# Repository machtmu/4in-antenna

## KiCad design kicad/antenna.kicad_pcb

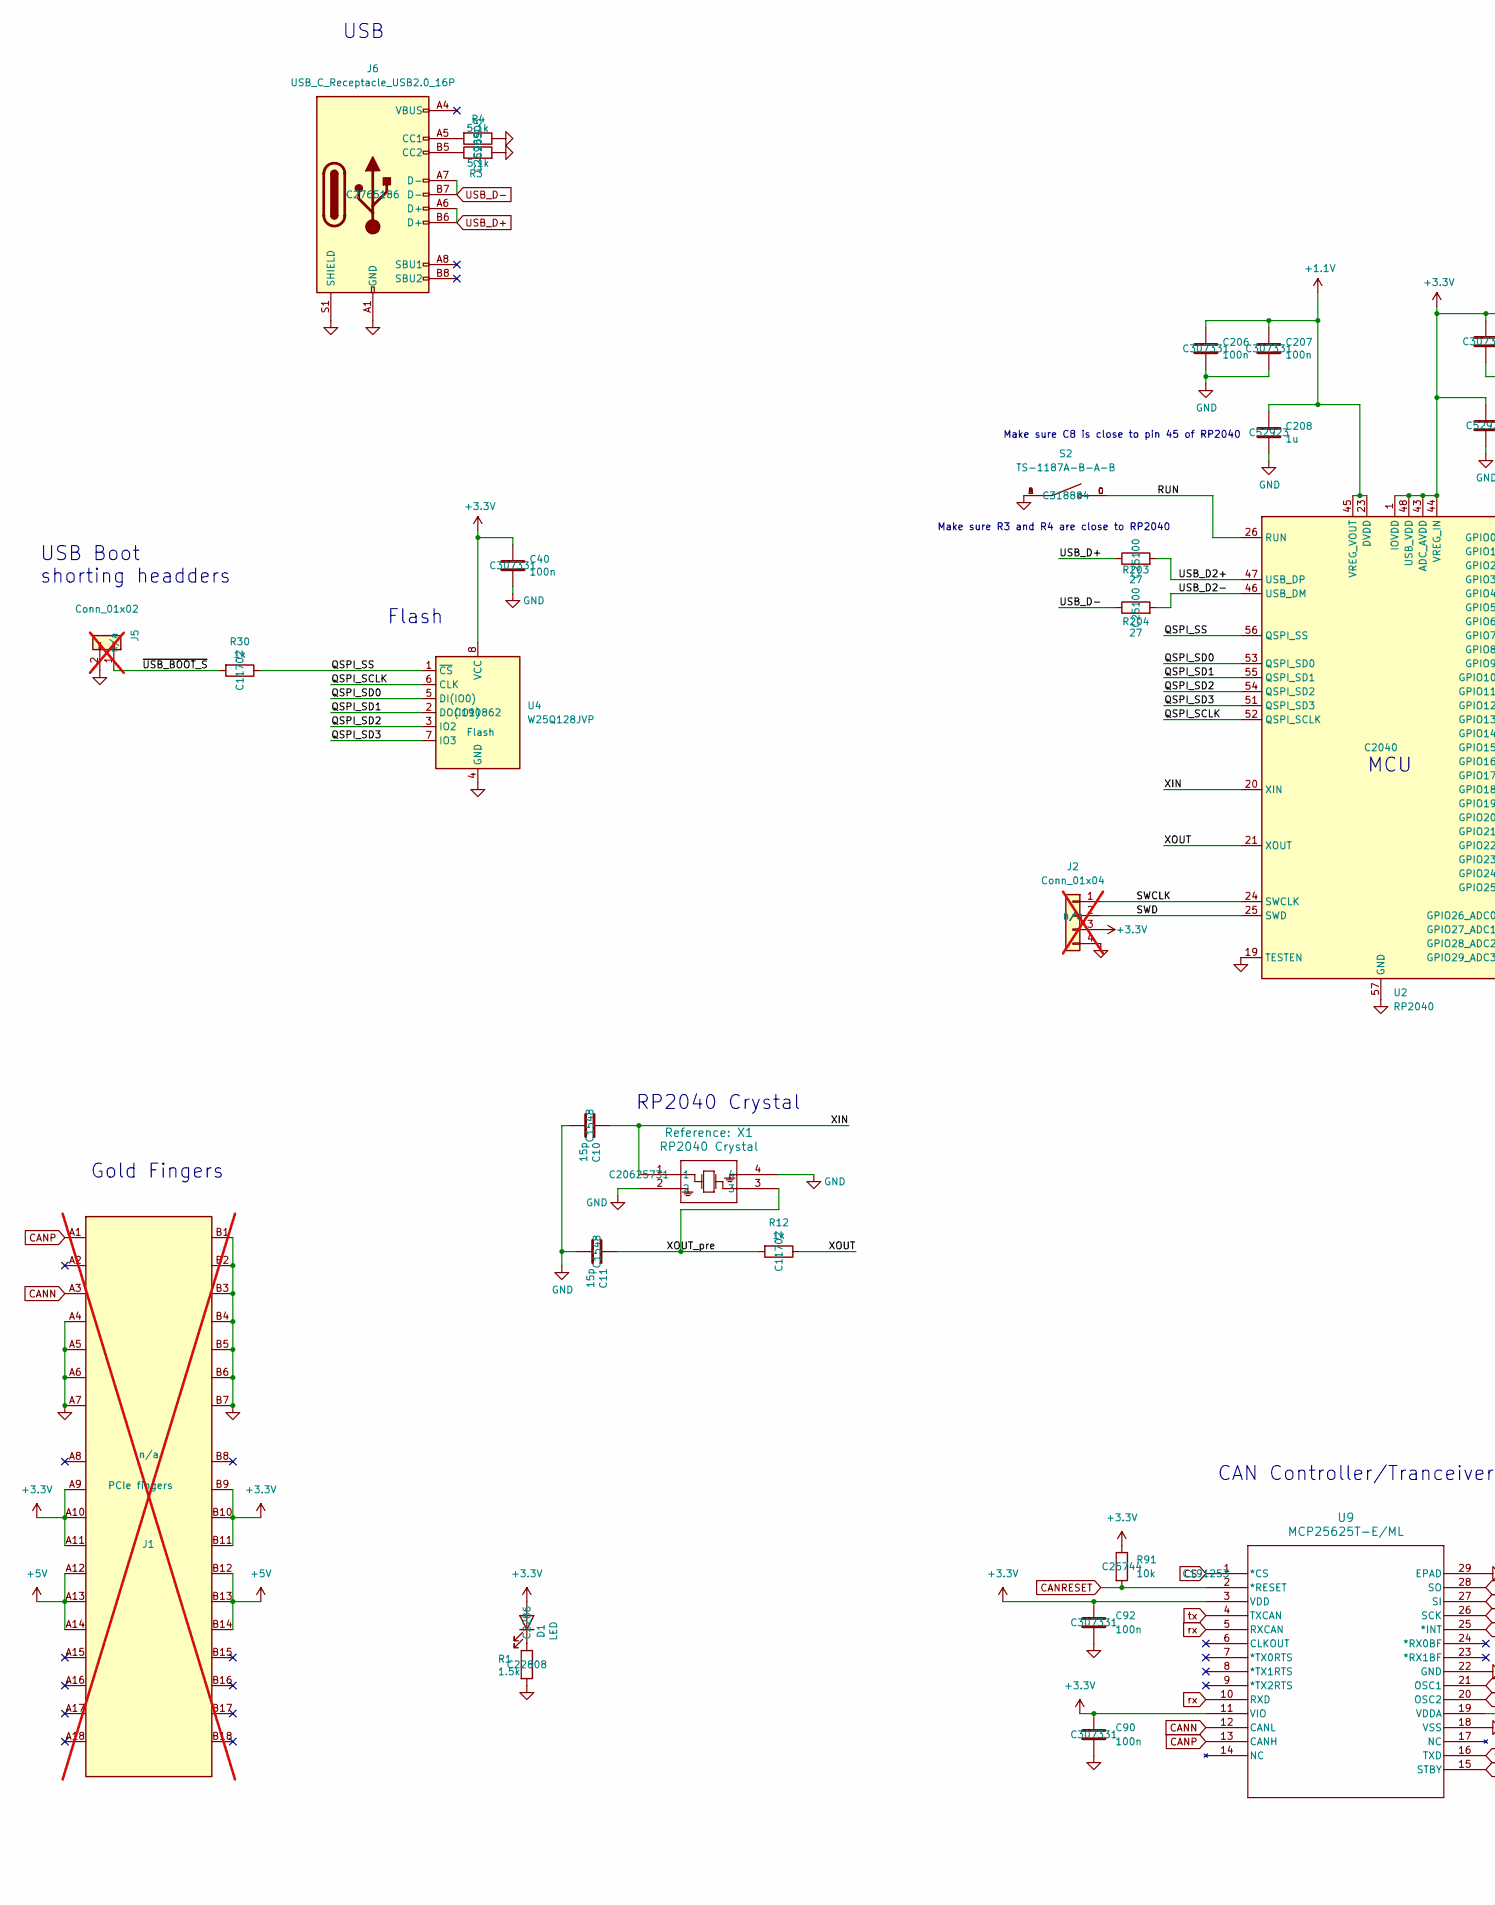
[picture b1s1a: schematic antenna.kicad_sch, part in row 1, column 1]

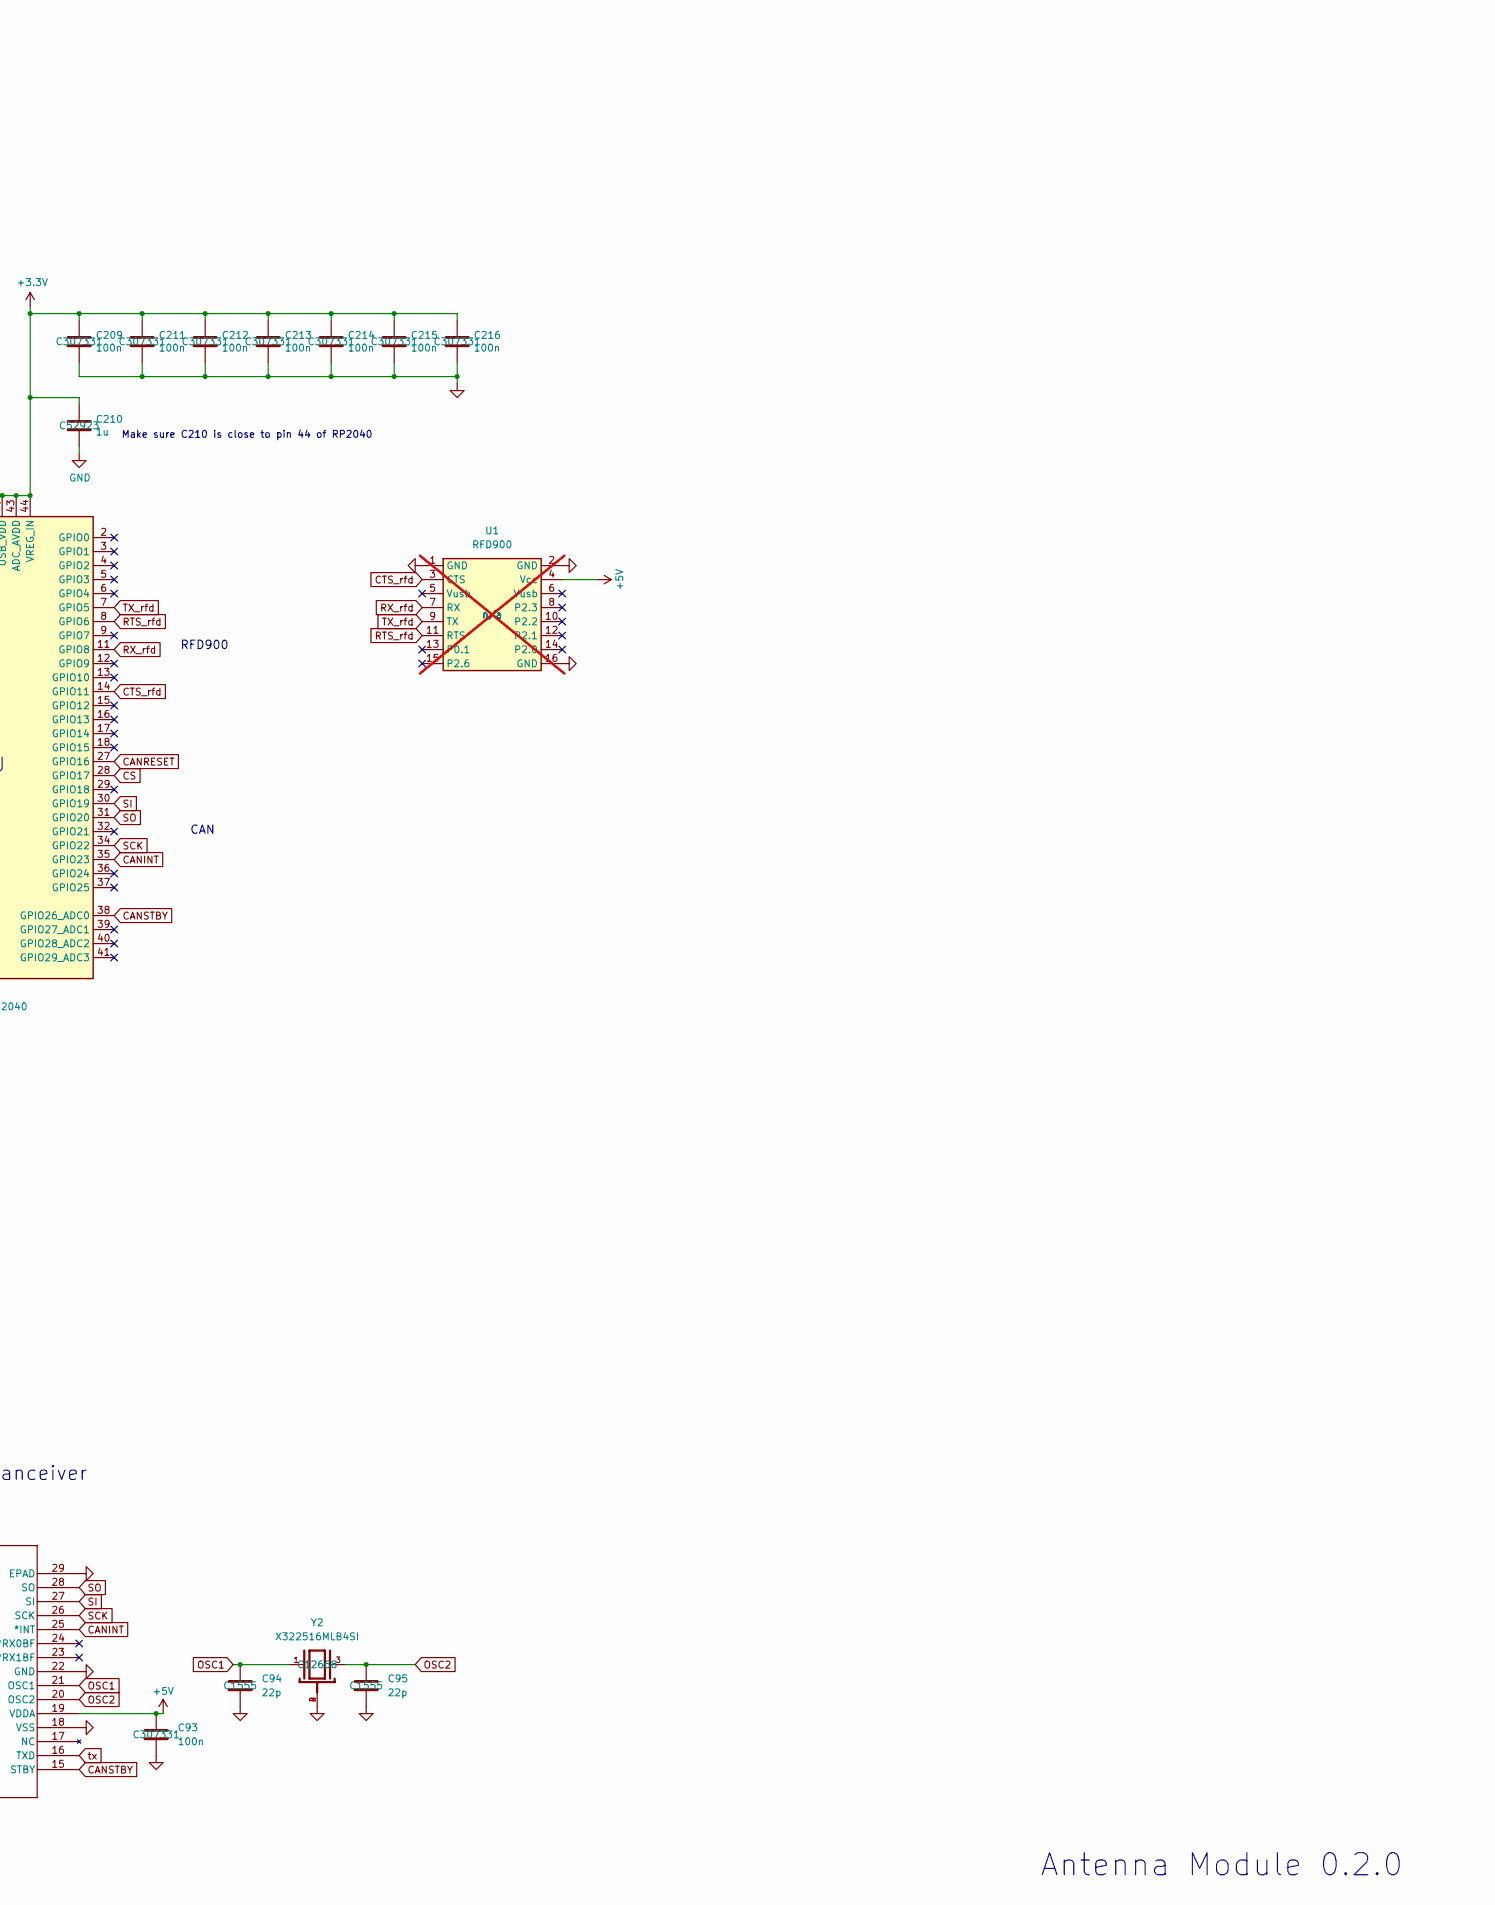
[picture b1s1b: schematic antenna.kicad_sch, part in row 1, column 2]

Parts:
C10, C11: 15p; C_0402_1005Metric; LCSC Part # C1548
C40, C90, C92, C93, C206, C207, C209, C211, C212, C213, C214, C215, C216: 100n; C_0402_1005Metric; LCSC Part # C307331
C94, C95: 22p; C_0402_1005Metric; LCSC Part # C1555
C208, C210: 1u; C_0402_1005Metric; LCSC Part # C52923
D1: LED; LED_0603_1608Metric; LCSC Part # C2286
J1: Bus_PCI_Express_x1; BUS_PCIexpress_x1; LCSC Part # n/a; not fitted
J2: Conn_01x04; NS-Tech_Grove_1x04_P2mm_Vertical; LCSC PN n/a; not fitted
J5: Conn_01x02; PinHeader_1x02_P2.54mm_Vertical; LCSC Part # n/a; not fitted
J6: USB_C_Receptacle_USB2.0_16P; USB_C_Receptacle_Palconn_UTC16-G; LCSC Part # C2765186
R1: 1.5k; R_0603_1608Metric; LCSC Part # C22808
R3, R4: 5.1k; R_0402_1005Metric; LCSC Part # C25905
R12, R30: 1k; R_0402_1005Metric; LCSC Part # C11702
R91: 10k; R_0402_1005Metric; LCSC Part # C25744
R203, R204: 27; R_0402_1005Metric; LCSC Part # C25100
S2: TS-1187A-B-A-B; Manufacturer PN TS-1187A-B-A-B; LCSC PN C318884
U1: RFD900; LCSC PN n/a; not fitted
U2: RP2040; QFN-56-1EP_7x7mm_P0.4mm_EP3.2x3.2mm; LCSC C2040
U4: W25Q128JVP; WSON-8-1EP_6x5mm_P1.27mm_EP3.4x4.3mm; LCSC C190862
U9: MCP25625T-E/ML; QFN28_6X6MC_MCH; LCSC PN C191253
X1: RP2040 Crystal; ABM8-272-T3_ABR; Manufacturer PN ABM8-272-T3_ABR; LCSC PN C20625731
Y2: X322516MLB4SI; LCSC PN C12668

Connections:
+1.1V: C206.1, C207.1, C208.1, U2.23 (DVDD), U2.45 (VREG_VOUT), U2.50 (DVDD)
+3.3V: C40.1, C90.1, C92.1, C209.1, C210.1, C211.1, C212.1, C213.1, C214.1, C215.1, C216.1, D1.2 (A), J1.A9 (+3.3V), J1.A10 (+3.3V), J1.A11 (~PERST), J1.B9 (JTAG1), J1.B10 (3.3Vaux), J1.B11 (~WAKE), J2.3, R91.1, U2.1 (IOVDD), U2.10 (IOVDD), U2.22 (IOVDD), U2.33 (IOVDD), U2.42 (IOVDD), U2.43 (ADC_AVDD), U2.44 (VREG_IN), U2.48 (USB_VDD), U2.49 (IOVDD), U4.8 (VCC), U9.3 (VDD), U9.11 (VIO)
+5V: C93.1, J1.A12 (GND), J1.A13 (REFCLK+), J1.A14 (REFCLK-), J1.B12 (RSVD), J1.B13 (GND), J1.B14 (PETp0), U1.4 (Vcc), U9.19 (VDDA)
/QSPI_SCLK: U2.52 (QSPI_SCLK), U4.6 (CLK)
/QSPI_SD0: U2.53 (QSPI_SD0), U4.5 (DI(IO0))
/QSPI_SD1: U2.55 (QSPI_SD1), U4.2 (DO(IO1))
/QSPI_SD2: U2.54 (QSPI_SD2), U4.3 (IO2)
/QSPI_SD3: U2.51 (QSPI_SD3), U4.7 (IO3)
/QSPI_SS: R30.1, U2.56 (QSPI_SS), U4.1 (~CS)
/RUN: S2.C, S2.D, U2.26 (RUN)
/SWCLK: J2.1, U2.24 (SWCLK)
/SWD: J2.2, U2.25 (SWD)
/USB_D2+: R203.2, U2.47 (USB_DP)
/USB_D2-: R204.2, U2.46 (USB_DM)
/XIN: C10.1, U2.20 (XIN), X1.1
/XOUT: R12.1, U2.21 (XOUT)
/XOUT_pre: C11.1, R12.2, X1.3
/~USB_BOOT_S: J5.1, R30.2
CANINT: U2.35 (GPIO23), U9.25 (*INT)
CANN: J1.A3 (+12V), U9.12 (CANL)
CANP: J1.A1 (~PRSNT1), U9.13 (CANH)
CANRESET: R91.2, U2.27 (GPIO16), U9.2 (*RESET)
CANSTBY: U2.38 (GPIO26_ADC0), U9.15 (STBY)
CS: U2.28 (GPIO17), U9.1 (*CS)
CTS_rfd: U1.3 (CTS), U2.14 (GPIO11)
GND: C10.2, C11.2, C40.2, C90.2, C92.2, C93.2, C94.2, C95.2, C206.2, C207.2, C208.2, C209.2, C210.2, C211.2, C212.2, C213.2, C214.2, C215.2, C216.2, J1.A4 (GND), J1.A5 (JTAG2), J1.A6 (JTAG3), J1.A7 (JTAG4), J1.B1 (+12V), J1.B2 (+12V), J1.B3 (+12V), J1.B4 (GND), J1.B5 (SMCLK), J1.B6 (SMDAT), J1.B7 (GND), J2.4, J5.2, J6.A1 (GND), J6.A12 (GND), J6.B1 (GND), J6.B12 (GND), J6.S1 (SHIELD), R1.2, R3.2, R4.1, S2.A, S2.B, U1.1 (GND), U1.2 (GND), U1.16 (GND), U2.19 (TESTEN), U2.57 (GND), U4.4 (GND), U9.18 (VSS), U9.22 (GND), U9.29 (EPAD), X1.2, X1.4, Y2.2, Y2.4
unnamed: D1.1 (K), R1.1
unnamed: J6.A5 (CC1), R4.2
unnamed: J6.B5 (CC2), R3.1
OSC1: C94.1, U9.21 (OSC1), Y2.1
OSC2: C95.1, U9.20 (OSC2), Y2.3
RTS_rfd: U1.11 (RTS), U2.8 (GPIO6)
RX_rfd: U1.7 (RX), U2.11 (GPIO8)
SCK: U2.34 (GPIO22), U9.26 (SCK)
SI: U2.30 (GPIO19), U9.27 (SI)
SO: U2.31 (GPIO20), U9.28 (SO)
TX_rfd: U1.9 (TX), U2.7 (GPIO5)
USB_D+: J6.A6 (D+), J6.B6 (D+), R203.1
USB_D-: J6.A7 (D-), J6.B7 (D-), R204.1
rx: U9.5 (RXCAN), U9.10 (RXD)
tx: U9.4 (TXCAN), U9.16 (TXD)

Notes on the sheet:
Make sure C210 is close to pin 44 of RP2040
Make sure C8 is close to pin 45 of RP2040
RP2040 Crystal
USB
Make sure R3 and R4 are close to RP2040
CAN
RFD900
USB Boot shorting headders
Antenna Module 0.2.0
Gold Fingers
MCU
CAN Controller/Tranceiver
Flash

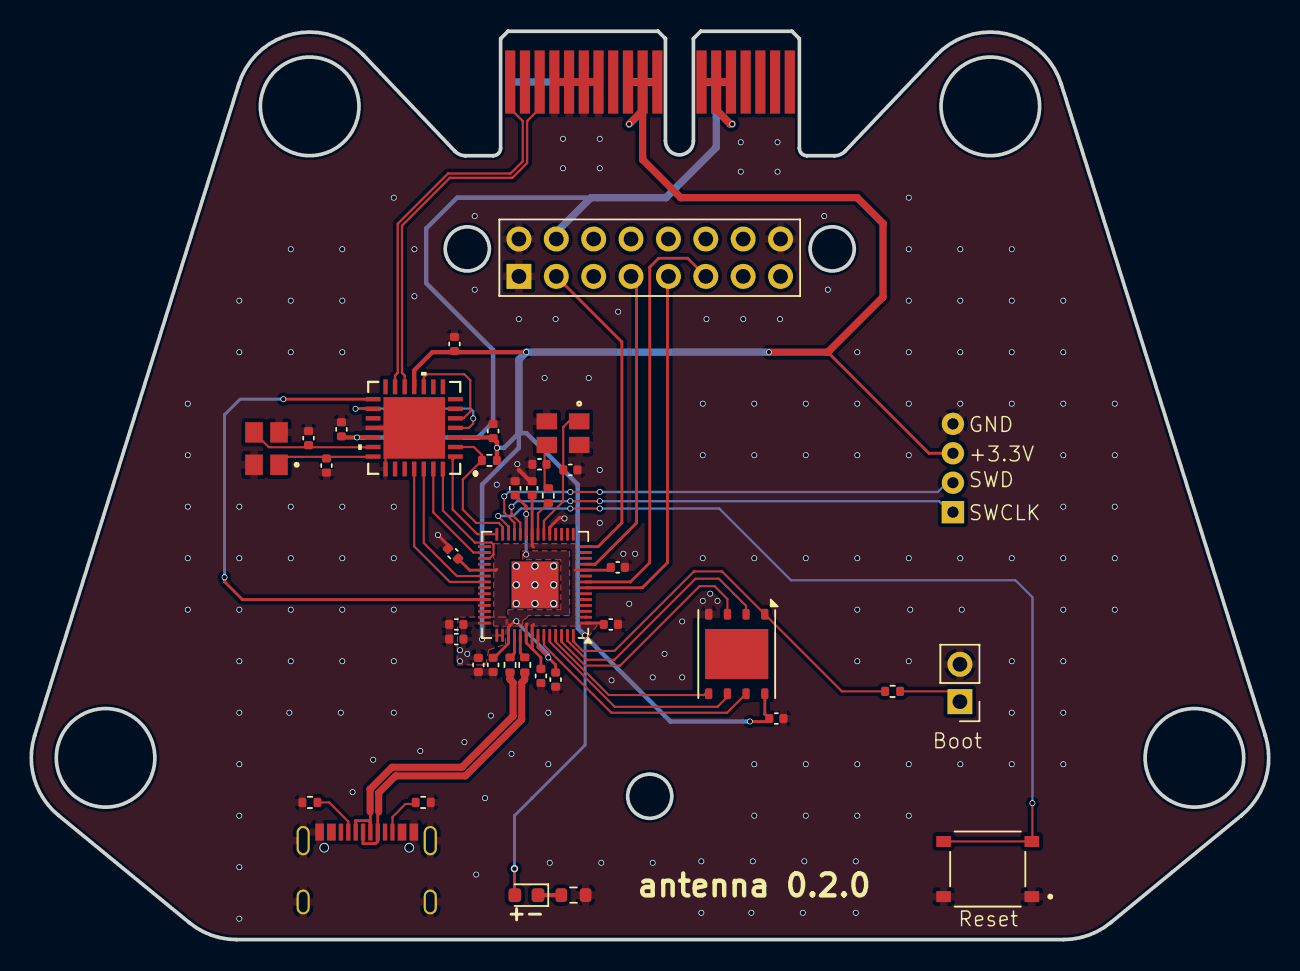
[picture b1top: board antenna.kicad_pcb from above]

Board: 2 copper layers, 84.1 x 61.7 mm, 39 parts (1 on the bottom side), 41 nets.

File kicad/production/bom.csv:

Designator,Footprint,Quantity,Value,LCSC Part #
"C10, C11",0402,2,15p,C1548
"C206, C207, C209, C211, C212, C213, C214, C215, C216, C40, C90, C92, C93",0402,13,100n,C307331
"C208, C210",0402,2,1u,C52923
"C94, C95",0402,2,22p,C1555
D1,0603,1,LED,C2286
J6,USB_C_Receptacle_Palconn_UTC16-G,1,USB_C_Receptacle_USB2.0_16P,C2765186
R1,0603,1,1.5k,C22808
"R12, R30",0402,2,1k,C11702
"R203, R204",0402,2,27,C25100
"R3, R4",0402,2,5.1k,C25905
R91,0402,1,10k,C25744
S2,TS-1187A-B-A-B,1,TS-1187A-B-A-B,C318884
U2,QFN-56-1EP_7x7mm_P0.4mm_EP3.2x3.2mm,1,RP2040,C2040
U4,WSON-8-1EP_6x5mm_P1.27mm_EP3.4x4.3mm,1,W25Q128JVP,C190862
U9,QFN28_6X6MC_MCH,1,MCP25625T-E/ML,C191253
X1,ABM8-272-T3_ABR,1,RP2040 Crystal,C20625731
Y2,X322516MLB4SI,1,X322516MLB4SI,C12668

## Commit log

2025-03-07 update mates, add new antenna files
2025-03-07 add **/~ to .gitignore
2025-03-07 update project to kicad 9, remove test label in title
2025-03-07 Update images
2025-03-07 update PCB from kicad
2025-03-07 update rfd board assembly
2025-03-07 supress antennas
2025-03-09 update assemblies
2025-03-25 Add ratsnest and grid layers to antenna.kicad_prl; update rfd_board2.SLDASM
2025-04-07 create RFD900 footprint, update schematic library to global
2025-04-07 route USB, add LED
2025-04-07 add new DXF of the rack
2025-04-08 finalize version 0.1.1 for ordering
2025-04-16 move flash away from mounting hole, update to text to 0.2.0
2025-04-16 export final production files for 0.2.0
2025-04-16 update project file
